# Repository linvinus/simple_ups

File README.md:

# simple_ups
simple uninterruptible power supply circuit

Подробное описание и обсуждение здесь http://roboforum.ru/forum11/topic2129-615.html#p351430

circuit created in eagle cad http://www.cadsoftusa.com/download-eagle/

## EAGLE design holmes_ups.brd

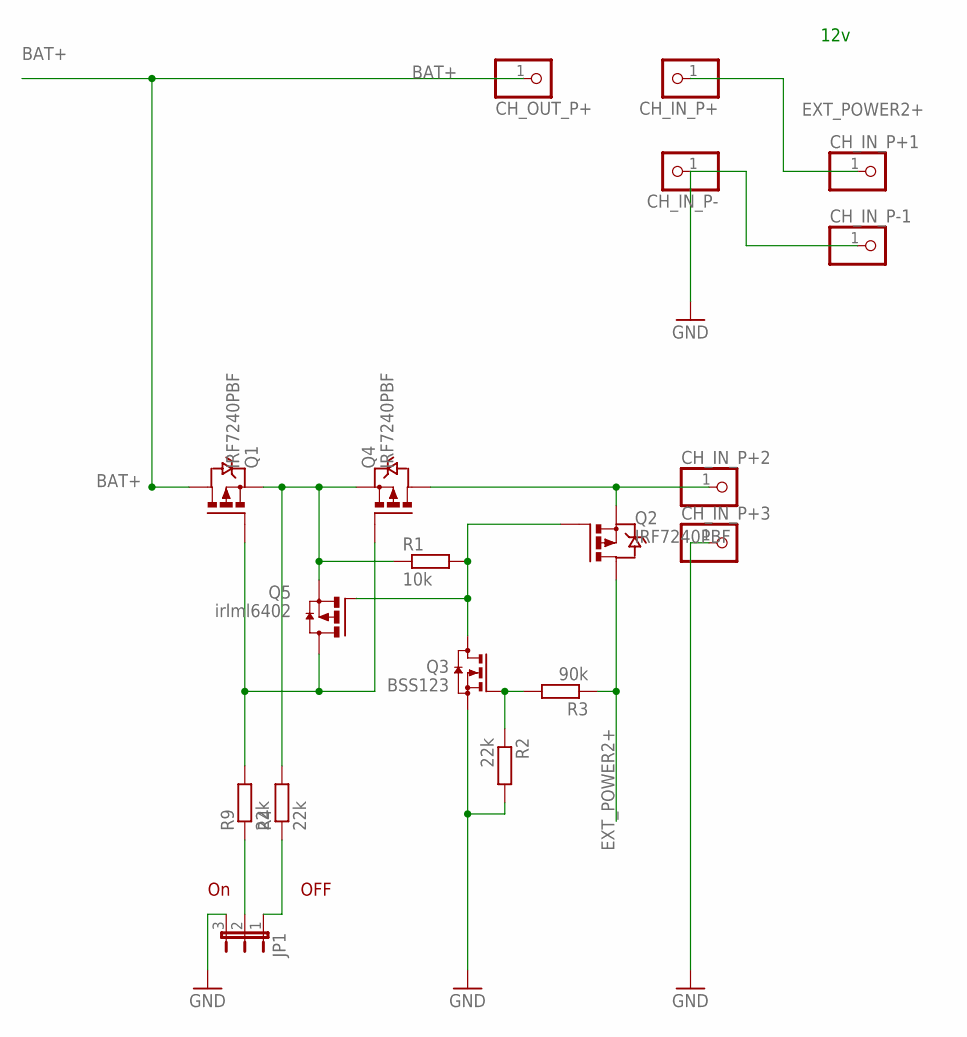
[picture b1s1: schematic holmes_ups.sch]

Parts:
CH_IN_P+, CH_IN_P+1, CH_IN_P+2, CH_IN_P+3: PINHD-1X1; 1X01
CH_IN_P-, CH_IN_P-1: PINHD-1X1; 1X01
CH_OUT_P+: PINHD-1X1; 1X01
JP1: JP2E; JP2
Q1, Q2, Q4: IRF7240PBF; SO-08
Q3: BSS123; SOT23
Q5: irlml6402; SUPER-SOT3
R1: 10k; R0805
R2, R4, R9: 22k; R0805
R3: 90k; R0805

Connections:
BAT+: CH_OUT_P+.1, Q1.5 (D), Q1.6 (D), Q1.7 (D), Q1.8 (D)
EXT_POWER2+: CH_IN_P+.1, CH_IN_P+1.1, Q2.5 (D), Q2.6 (D), Q2.7 (D), Q2.8 (D), R3.1
GND: CH_IN_P+3.1, CH_IN_P-.1, CH_IN_P-1.1, JP1.3, Q3.2 (S), R2.2
unnamed: Q2.4 (G), Q3.3 (D), Q5.1 (G), R1.2
unnamed: Q3.1 (G), R2.1, R3.2
unnamed: JP1.2, R9.1
unnamed: Q1.1 (S), Q1.2 (S), Q1.3 (S), Q4.1 (S), Q4.2 (S), Q4.3 (S), Q5.2 (S), R1.1, R4.2
unnamed: CH_IN_P+2.1, Q2.1 (S), Q2.2 (S), Q2.3 (S), Q4.5 (D), Q4.6 (D), Q4.7 (D), Q4.8 (D)
unnamed: JP1.1, R4.1
unnamed: Q1.4 (G), Q4.4 (G), Q5.3 (D), R9.2

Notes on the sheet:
12v
OFF

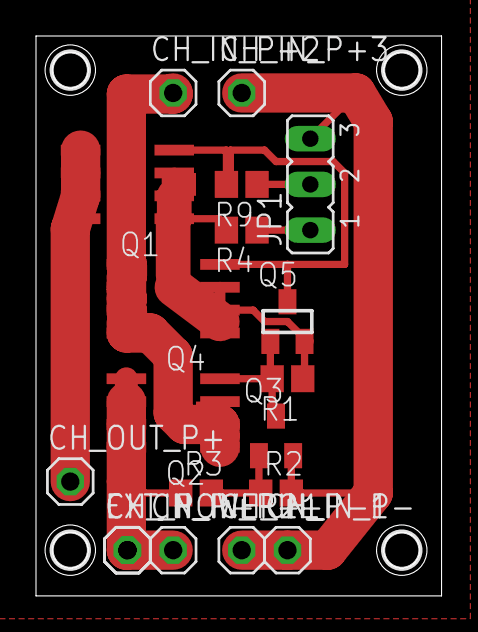
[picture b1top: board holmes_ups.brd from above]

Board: 2 copper layers, 22.5 x 31.1 mm, 23 parts (0 on the bottom side), 10 nets.

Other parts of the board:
EXT_POWER2+: 1X01
U$1, U$2, U$3, U$4: 2

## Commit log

2016-04-03 add .gitignore
2016-04-03 improve .gitignore
2016-04-03 initial public release
2016-04-08 fix, completely close Q4 if vbatt > external power
2016-04-08 fix v2, completely close Q4 if vbatt > external power
2016-04-14 special for holmes
